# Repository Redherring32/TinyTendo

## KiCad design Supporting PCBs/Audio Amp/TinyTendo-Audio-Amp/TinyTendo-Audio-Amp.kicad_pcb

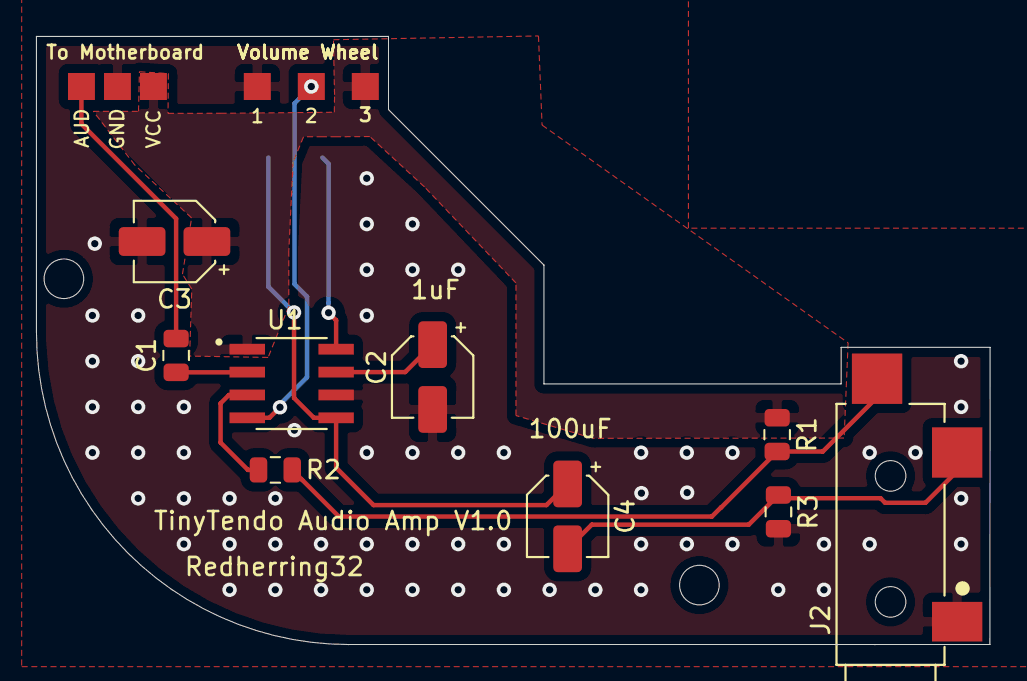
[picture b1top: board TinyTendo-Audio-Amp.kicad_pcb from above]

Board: 2 copper layers, 53.0 x 33.8 mm, 14 parts (0 on the bottom side), 11 nets.

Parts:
 : MountingHole_2.2mm_M2
 #2: MountingHole_2.2mm_M2
C1: 0.22uF; C_0805_2012Metric
C2, C3: 1uF; CP_Elec_4x5.8
C4: 100uF; CP_Elec_4x5.8
J1: Conn_Coaxial; AUD-IN
J2: MJ-3523-SMT; CUI_MJ-3523-SMT
LS1: Speaker
R1, R2: 100K; R_0805_2012Metric
R3: 150R; R_0805_2012Metric
U1: LM4865M; SOIC127P599X175-8N
Volume Wheel: 10K; VolPot

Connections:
/GND: C2.2, C3.2, J1.2, J2.1, R3.2, U1.6, Volume Wheel.3
/VDD: C3.1, J1.3, R1.1, U1.1, Volume Wheel.1
unnamed: C1.1, U1.2
unnamed: C1.2, J1.1
unnamed: C2.1, U1.7
unnamed: C4.1, LS1.1, U1.5
unnamed: C4.2, J2.2, R3.1
unnamed: J2.10, R1.2, R2.1
unnamed: LS1.2, U1.8
unnamed: R2.2, U1.3
unnamed: U1.4, Volume Wheel.2

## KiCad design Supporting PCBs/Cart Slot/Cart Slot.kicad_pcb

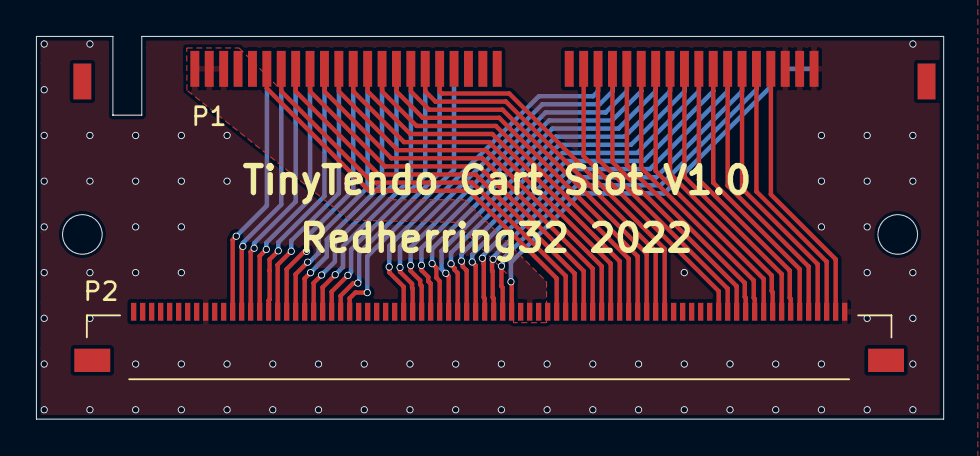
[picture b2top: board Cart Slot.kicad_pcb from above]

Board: 2 copper layers, 50.4 x 21.3 mm, 4 parts (0 on the bottom side), 56 nets.

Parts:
 : MountingHole_2.2mm_M2
 #2: MountingHole_2.2mm_M2
P1: 72-Pin Connector; Cart Slot
P2: 72-Pin Connector; 5051108091

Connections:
/CPU-A0: P1.13, P2.13
/CPU-A1: P1.12, P2.12
/CPU-A2: P1.11, P2.11
/CPU-A3: P1.10, P2.10
/CPU-A4: P1.9, P2.9
/CPU-A5: P1.8, P2.8
/CPU-A6: P1.7, P2.7
/CPU-A7: P1.6, P2.6
/CPU-A8: P1.5, P2.5
/CPU-A9: P1.4, P2.4
/CPU-A10: P1.3, P2.3
/CPU-A11: P1.2, P2.2
/CPU-A12: P1.39, P2.39
/CPU-A13: P1.40, P2.40
/CPU-A14: P1.41, P2.41
/CPU-D0: P1.49, P2.49
/CPU-D1: P1.48, P2.48
/CPU-D2: P1.47, P2.47
/CPU-D3: P1.46, P2.46
/CPU-D4: P1.45, P2.45
/CPU-D5: P1.44, P2.44
/CPU-D6: P1.43, P2.43
/CPU-D7: P1.42, P2.42
/CPU-R~W: P1.14, P2.14
/GND: P1.1, P1.72, P2.1, P2.72
/M2: P1.38, P2.38
/PPU-A0: P1.29, P2.29
/PPU-A1: P1.28, P2.28
/PPU-A2: P1.27, P2.27
/PPU-A3: P1.26, P2.26
/PPU-A4: P1.25, P2.25
/PPU-A5: P1.24, P2.24
/PPU-A6: P1.23, P2.23
/PPU-A7: P1.59, P2.59
/PPU-A8: P1.60, P2.60
/PPU-A9: P1.61, P2.61
/PPU-A10: P1.63, P2.63
/PPU-A11: P1.62, P2.62
/PPU-A12: P1.64, P2.64
/PPU-A13: P1.65, P2.65
/PPU-D0: P1.30, P2.30
/PPU-D1: P1.31, P2.31
/PPU-D2: P1.32, P2.32
/PPU-D3: P1.33, P2.33
/PPU-D4: P1.69, P2.69
/PPU-D5: P1.68, P2.68
/PPU-D6: P1.67, P2.67
/PPU-D7: P1.66, P2.66
/PPU-~A13: P1.58, P2.58
/PPU-~RD: P1.21, P2.21
/PPU-~WE: P1.56, P2.56
/VCC: P1.36, P2.36
/VRAM-A10: P1.22, P2.22
/VRAM-~CE: P1.57, P2.57
/~IRQ: P1.15, P2.15
/~ROMSEL: P1.50, P2.50

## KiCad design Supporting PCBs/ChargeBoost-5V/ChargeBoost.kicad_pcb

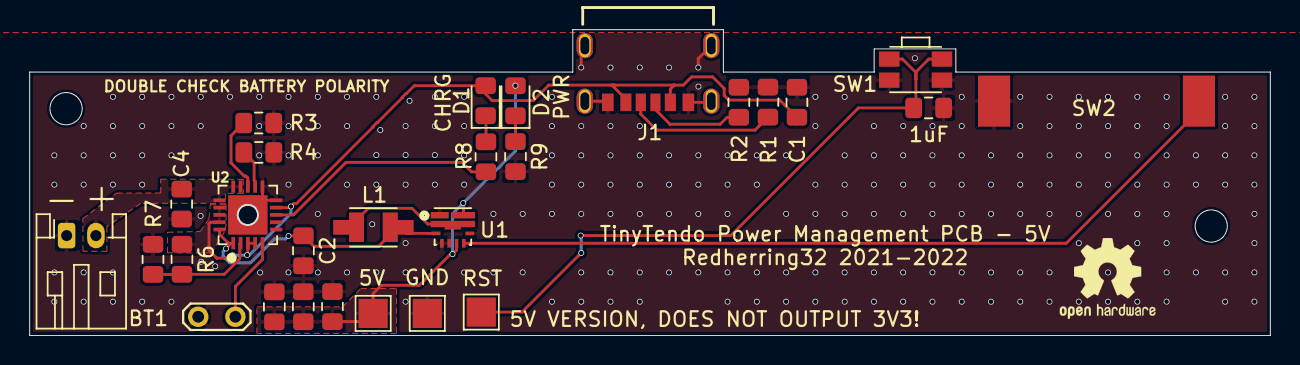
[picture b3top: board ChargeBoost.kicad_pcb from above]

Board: 2 copper layers, 84.8 x 20.9 mm, 30 parts (0 on the bottom side), 17 nets.

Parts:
 : 1uF; C_0805_2012Metric_Pad1.15x1.40mm_HandSolder
 #2,  #3: MountingHole_2.2mm_M2
BT1: 2800mAh; JST_PH_S2B-PH-K_1x02_P2.00mm_Horizontal-Mirrored
C1, C2, C4: 10uF; C_0805_2012Metric_Pad1.15x1.40mm_HandSolder
C3, C5, C6: 22uF; C_0805_2012Metric_Pad1.15x1.40mm_HandSolder
D1: Red; LED_0805_2012Metric_Pad1.15x1.40mm_HandSolder
D2: BLUE; LED_0805_2012Metric_Pad1.15x1.40mm_HandSolder
J1: USB4125-GF-A_REVA2; GCT_USB4125-GF-A_REVA2
J3, J4, J5: Conn_01x01_Male; TestPoint_Pad_2.0x2.0mm
L1: 1uH; IND_LQH32CN1R0M23L
R1, R2: 5K1; R_0805_2012Metric_Pad1.15x1.40mm_HandSolder
R3, R8: 1K; R_0805_2012Metric_Pad1.15x1.40mm_HandSolder
R4, R7: 100K; R_0805_2012Metric_Pad1.15x1.40mm_HandSolder
R6: 270K; R_0805_2012Metric_Pad1.15x1.40mm_HandSolder
R9: 91R; R_0805_2012Metric_Pad1.15x1.40mm_HandSolder
SW1: SW_Push; SW_SPST_EVQP7A
SW2: PWR
THERM1: 15K; TestPoint_2Pads_Pitch2.54mm_Drill0.8mm
U1: TPS61235PRWLT; CONV_TPS61235PRWLT
U2: MCP73871-2AAI_ML; QFN50P400X400X100-21N

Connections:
/GND: .2, BT1.2, C1.2, C2.2, C3.2, C4.2, C5.2, C6.2, J1.A12, J1.B12, J1.S1, J3.1, R1.2, R2.2, R3.2, R4.2, R7.2, R9.2, SW1.1, SW2.1, THERM1.2, U1.1, U1.4, U1.5, U1.8, U2.10, U2.11, U2.21
/RST: .1, J5.1, SW1.2
/VBAT: C2.1, L1.1, U1.3, U2.1, U2.20
/VBUS: C1.1, D1.2, J1.A9, J1.B9, R6.1, U2.3, U2.4, U2.9, U2.17, U2.18, U2.19
/VOUT: C3.1, C5.1, C6.1, D2.2, J4.1, U1.6, U1.9
unnamed: BT1.1, C4.1, U2.14, U2.15, U2.16
unnamed: D1.1, R8.1
unnamed: D2.1, R9.1
unnamed: J1.A5, R2.1
unnamed: J1.B5, R1.1
unnamed: L1.2, U1.2
unnamed: R3.1, U2.13
unnamed: R4.1, U2.12
unnamed: R6.2, R7.1, U2.2
unnamed: R8.2, U2.8
unnamed: SW2.2, U1.7
unnamed: THERM1.1, U2.5

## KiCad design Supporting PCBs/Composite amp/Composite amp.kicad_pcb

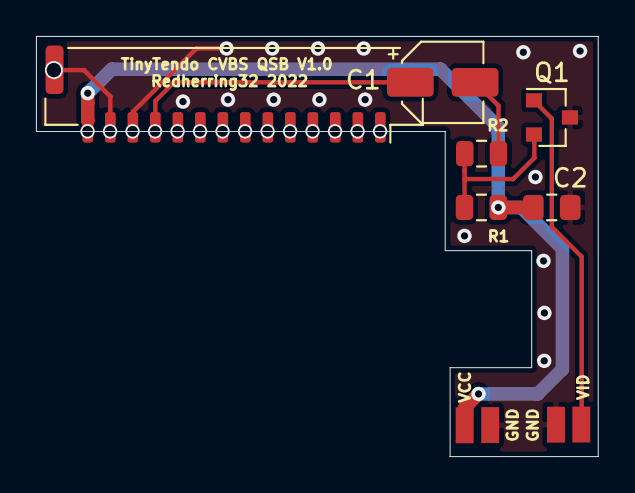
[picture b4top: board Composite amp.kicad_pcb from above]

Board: 2 copper layers, 31.2 x 23.3 mm, 10 parts (0 on the bottom side), 6 nets.

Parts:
C1: 100uF; CP_Elec_4x4.5
C2: 22uF; C_0805_2012Metric_Pad1.15x1.40mm_HandSolder
GND1, GND2: TestPoint; SolderPad
J1: Conn_01x14_Female; JST_GH_SM14B-GHS-TB_1x14-1MP_P1.25mm_Horizontal
Q1: MMBT3906; SOT-23
R1: 300R; R_0805_2012Metric
R2: 110R; R_0805_2012Metric
VCC1: TestPoint; SolderPad
VID1: TestPoint; SolderPad

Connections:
/5V: C2.1, J1.14, R1.1, VCC1.1
/GND: C2.2, GND1.1, GND2.1, J1.12, J1.13, Q1.3
/VIDEO-IN: Q1.1, VID1.1
/VIDEO-OUT: C1.1, J1.11
unnamed: C1.2, R2.1
unnamed: Q1.2, R1.2, R2.2
